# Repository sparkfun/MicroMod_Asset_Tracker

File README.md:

# MicroMod Asset Tracker Carrier Board

[*SparkFun MicroMod Asset Tracker Carrier Board (DEV-17272)*](https://www.sparkfun.com/products/17272)

The MicroMod Asset Tracker Carrier Board provides you with a toolkit to monitor and track the location of your assets. Built around the u-blox SARA-R510M8S module, the asset tracker offers Secure Cloud LTE-M data communication for multi-regional use and has an integrated u-blox M8 GNSS receiver for accurate positioning information. The SARA-R5 supports many different forms of data communication from full TCP/IP sockets and packet switched data, through HTTP Get/Put/Post, FTP (the SARA has a built-in file system), Ping, to good old SMS text messaging!

The Asset Tracker Carrier Board has an integrated ICM-20948 Inertial Measurement Unit (IMU) for Nine Degree-Of-Freedom orientation and movement detection. Want to send a message if your asset is moved? The Asset Tracker can do that! The board also has a built-in digital microphone and so can send an alert as soon as a noise is detected too.

The SparkFun Asset Tracker Carrier Board also has a built-in micro-SD card socket for data logging. Power options include both USB-C and LiPo battery (with built-in charging and battery fuel gauge), but you can provide power via a breakout pin too.

## Repository Contents

* **/Examples** - A set of examples demonstrating how to use each component on the Asset Tracker. Run these from the Arduino IDE.
* **/Documentation** - Datasheets etc.
* **/Hardware** - Eagle PCB, SCH and LBR design files. Full schematic in PDF format.
* **[LICENSE.md](./LICENSE.md)** - License details

## Documentation

* **[SparkFun u-blox SARA-R5 Arduino Library](https://github.com/sparkfun/SparkFun_u-blox_SARA-R5_Arduino_Library)** - An Arduino library for the SARA-R5 Module
* **[Hookup Guide](https://learn.sparkfun.com/tutorials/micromod-asset-tracker-carrier-board-hookup-guide)** - Basic Hookup Guide for the MicroMod Asset Tracker Carrier Board
* **[Getting Started with MicroMod](https://learn.sparkfun.com/tutorials/getting-started-with-micromod)** -  A tutorial to help you get started with the MicroMod Ecosystem.
* **[Designing with MicroMod](https://learn.sparkfun.com/tutorials/designing-with-micromod)** - A tutorial to walk you through the specs of the MicroMod processor and carrier board as well as the basics of incorporating the MicroMod form factor into your own PCB designs.

## Product Versions

* [DEV-17272](https://www.sparkfun.com/products/17272) - The MicroMod Asset Tracker Carrier Board uses the u-blox SARA-R5 LTE-M / NB-IoT module to provide a powerful development tool.

## License Information

This product is _**open source**_!

Please review the LICENSE.md file for license information.

If you have any questions or concerns on licensing, please contact technical support on our [SparkFun forums](https://forum.sparkfun.com/viewforum.php?f=152).

Distributed as-is; no warranty is given.

- Your friends at SparkFun.

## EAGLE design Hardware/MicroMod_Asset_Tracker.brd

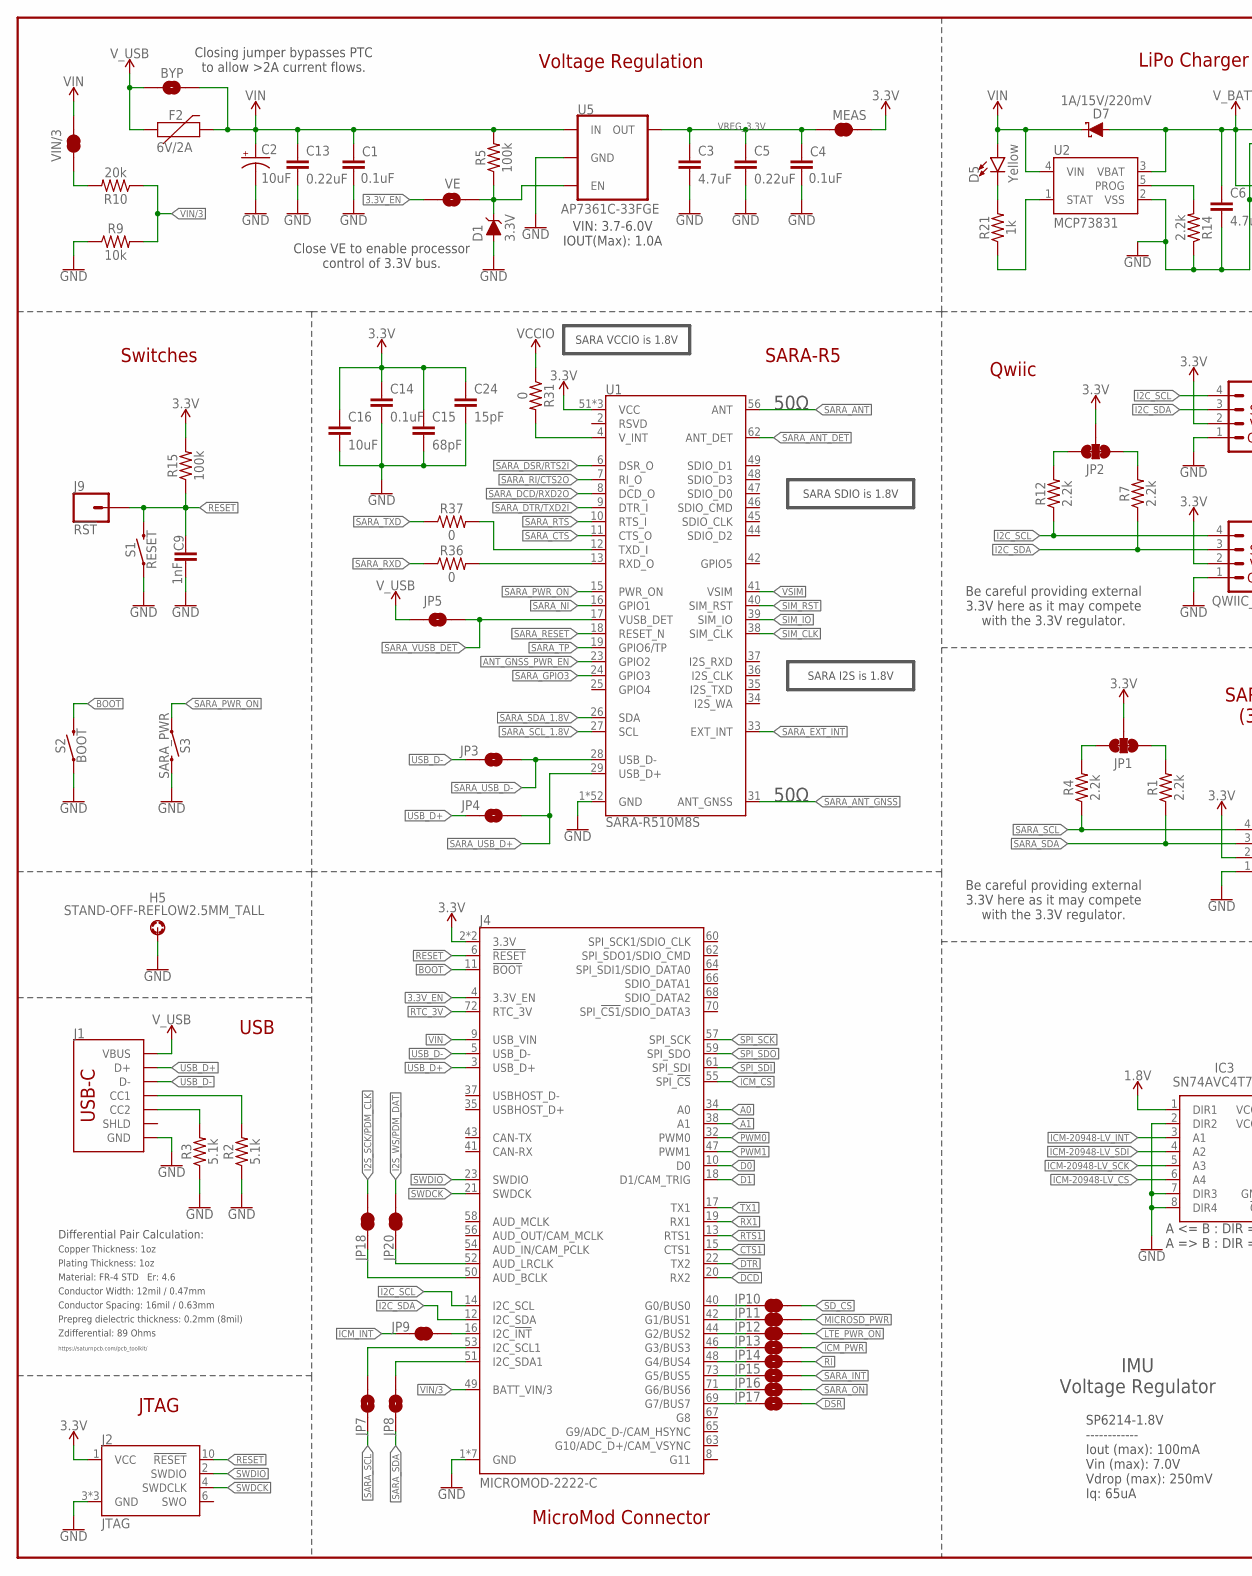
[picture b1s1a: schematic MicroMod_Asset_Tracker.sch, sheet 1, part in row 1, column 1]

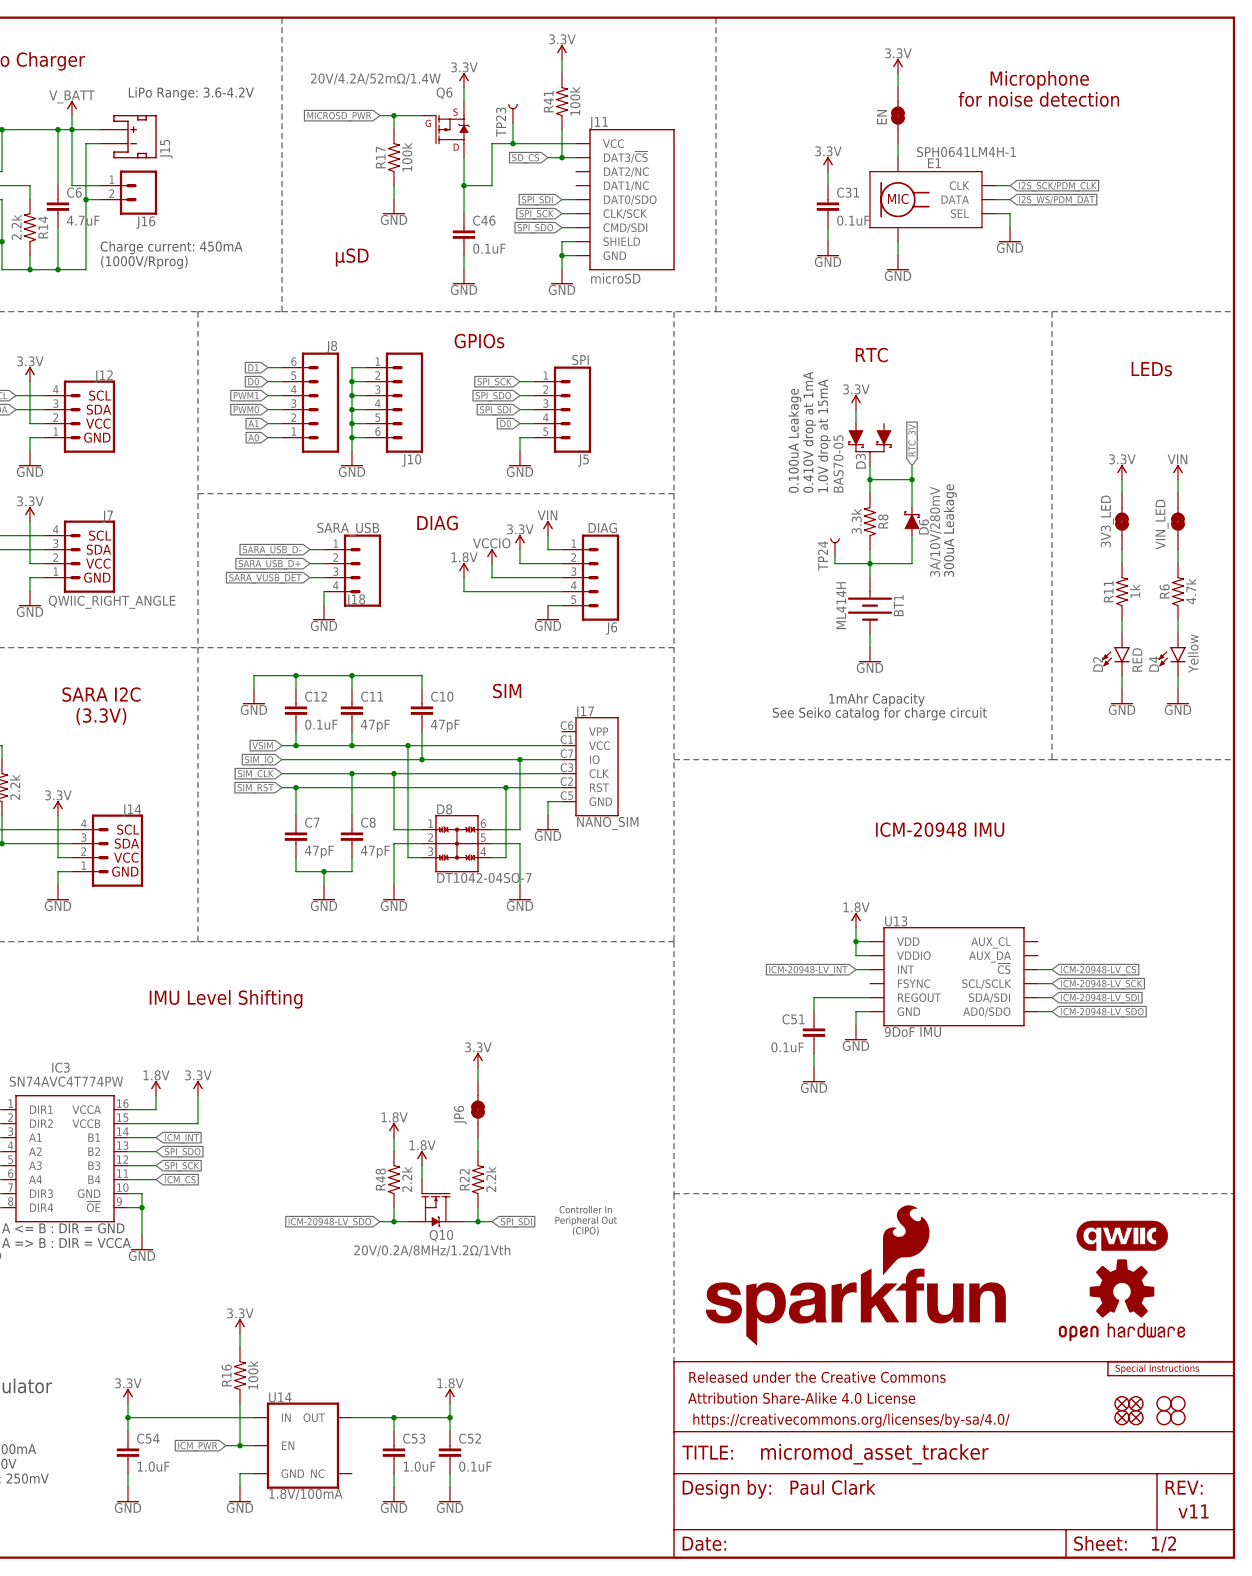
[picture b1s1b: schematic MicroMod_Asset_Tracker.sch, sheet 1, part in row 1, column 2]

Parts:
3V3_LED: JUMPER-SMT_2_NC_TRACE_SILK; SMT-JUMPER_2_NC_TRACE_SILK
BT1: ML414H; ML414H_IV01E
BYP: JUMPER-SMT_2_NO_SILK; SMT-JUMPER_2_NO_SILK
C1, C4, C12, C14, C31, C46, C51, C52: 0.1uF; 0603
C2: 10uF; EIA3216
C3, C6: 4.7uF; 0603
C5, C13: 0.22uF; 0603
C7, C8, C10, C11: 47pF; 0603
C9: 1nF; 0603
C15: 68pF; 0603
C16: 10uF; 0603
C24: 15pF; 0603
C53, C54: 1.0uF; 0603
D1: 3.3V; SOD-323
D2: RED; LED-0603
D3: BAS70-05; SOT23-3
D4, D5: Yellow; LED-0603
D6: 3A/10V/280mV; SOD-323
D7: 1A/15V/220mV; DO-214BA
D8: DT1042-04SO-7; SOT23-6L
E1: SPH0641LM4H-1; SPH0641LM4H-1_MICROPHONE
EN: JUMPER-SMT_2_NC_TRACE_SILK; SMT-JUMPER_2_NC_TRACE_SILK
F2: 6V/2A; 1210
FD1, FD2, FD3, FD4: FIDUCIALUFIDUCIAL; FIDUCIAL-MICRO
FRAME1: FRAME-LEDGER; CREATIVE_COMMONS
H1, H2, H3, H4: STAND-OFF
H5: STAND-OFF-REFLOW2.5MM_TALL; STAND-OFF-REFLOW-M2.5
IC3: SN74AVC4T774PW; SOP65P640X120-16N
J1: USB_C_4-LAYER_PADS; USB-C-16P_4LAYER-PADS
J2: JTAG; 2X5-PTH-1.27MM
J4: MICROMOD-2222-C; M.2-CONNECTOR-E
J5: SPI; 1X05_NO_SILK
J6: DIAG; 1X05_NO_SILK
J7: QWIIC_RIGHT_ANGLE; JST04_1MM_RA
J8, J10: CONN_06NO_SILK_NO_POP; 1X06_NO_SILK
J9: !RST!; 1X01_NO_SILK
J11: microSD; MICRO-SD-SOCKET
J12, J14: I2C_STANDARD_NO_SILK; 1X04_NO_SILK
J15: JST_2MM_MALE; JST-2-SMD
J16: CONN_021X02_NO_SILK; 1X02_NO_SILK
J17: NANO_SIM; NANO_SIM_WURTH_693043020611
J18: SARA_USB; 1X04_NO_SILK
JP1, JP2: JUMPER-SMT_3_2-NC_TRACE_SILK; SMT-JUMPER_3_2-NC_TRACE_SILK
JP3, JP4, JP5, JP7, JP8, JP13, JP14, JP15, JP16, JP17: JUMPER-SMT_2_NO_SILK; SMT-JUMPER_2_NO_SILK
JP6, JP9, JP10, JP11, JP12, JP18, JP20: JUMPER-SMT_2_NC_TRACE_SILK; SMT-JUMPER_2_NC_TRACE_SILK
LOGO1: SFE_LOGO_NAME_FLAME.1_INCH; SFE_LOGO_NAME_FLAME_.1
LOGO2: QWIIC_LOGO_CONNECTOR; QWIIC_5.5MM
LOGO3: OSHW-LOGOMINI; OSHW-LOGO-MINI
LOGO5: SPECIAL_INSTRUCTIONS-ORDERING; ORDERING_INSTRUCTIONS
MEAS: JUMPER-COMBO_2_NC_TRACE; COMBO-JUMPER_2_NC_TRACE
Q6: 20V/4.2A/52mΩ/1.4W; SOT23-3
Q10: 20V/0.2A/8MHz/1.2Ω/1Vth; SOT-416FL
R1, R4, R7, R12, R14, R22, R48: 2.2k; 0603
R2, R3: 5.1k; 0603
R5, R15, R16, R17, R41: 100k; 0603
R6: 4.7k; 0603
R8: 3.3k; 0603
R9: 10k; 0603
R10: 20k; 0603
R11, R21: 1k; 0603
R31, R36, R37: 0; 0603
S1: RESET; TACTILE_SWITCH_SMD_5.2MM
S2: BOOT; TACTILE_SWITCH_SMD_5.2MM
S3: SARA_PWR; TACTILE_SWITCH_SMD_5.2MM
TP23, TP24: TEST-POINT3; PAD.03X.03
U1: SARA-R510M8S; SARA-LGA
U2: MCP73831; SOT23-5
U5: AP7361C-33FGE; UDFN-8
U13: 9DoF IMU; QFN24-3X3-ICM-20948
U14: 1.8V/100mA; SC70
VE: JUMPER-SMT_2_NO_SILK; SMT-JUMPER_2_NO_SILK
VIN/3: JUMPER-SMT_2_NC_TRACE_SILK; SMT-JUMPER_2_NC_TRACE_SILK
VIN_LED: JUMPER-SMT_2_NC_TRACE_SILK; SMT-JUMPER_2_NC_TRACE_SILK

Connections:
1.8V: C52.1, C53.1, IC3.1 (DIR1), IC3.16 (VCCA), J6.4, Q10.1 (G), R48.2, U13.8 (VDDIO), U13.13 (VDD), U14.5 (OUT)
3.3V: 3V3_LED.2, C14.1, C15.1, C16.1, C24.1, C31.1, C54.1, D3.2 (A1), EN.2, IC3.15 (VCCB), J2.1 (VCC), J4.2 (3.3V), J4.74 (3.3V), J6.2, J7.2, J12.2, J14.2, JP1.2, JP2.2, JP6.2, MEAS.2, MEAS.4 (2), Q6.2 (S), R15.2, R16.2, R41.2, U1.51 (VCC), U1.52 (VCC), U1.53 (VCC), U14.1 (IN); also elsewhere on the board
3.3V_EN: J4.4 (3.3V_EN), VE.1
!BOOT!: J4.11 (!BOOT!), S2.3 (2), S2.4 (2)
!RESET!: C9.1, J2.10 (!RESET), J4.6 (!RESET!), J9.1, R15.1, S1.3 (2), S1.4 (2); also elsewhere on the board
A0: J4.34 (A0), J8.1
A1: J4.38 (A1), J8.2
ANT_GNSS_PWR_EN: U1.23 (GPIO2); also elsewhere on the board
CHG_LED: R21.1, U2.1 (STAT)
CTS1: J4.15 (CTS1); also elsewhere on the board
D0: J4.10 (D0), J5.4, J8.5
D1: J4.18 (D1/CAM_TRIG), J8.6
DCD: J4.20 (RX2); also elsewhere on the board
DSR: JP17.2; also elsewhere on the board
DTR: J4.22 (TX2); also elsewhere on the board
G0: J4.40 (G0/BUS0), JP10.1
G1: J4.42 (G1/BUS1), JP11.1
G2: J4.44 (G2/BUS2), JP12.1
G3: J4.46 (G3/BUS3), JP13.1
G4: J4.48 (G4/BUS4), JP14.1
G5: J4.73 (G5/BUS5), JP15.1
G6: J4.71 (G6/BUS6), JP16.1
G7: J4.69 (G7/BUS7), JP17.1
GND: BT1.-, C1.2, C2.-, C3.2, C4.2, C5.2, C6.2, C7.2, C8.2, C9.2, C10.1, C11.1, C12.1, C13.2, C14.2, C15.2, C16.2, C24.2, C31.2, C46.2, C51.2, C52.2, C53.2, C54.2, D1.A, D2.C, D4.C, D8.2, D8.5, E1.2 (SEL), E1.3 (GND), E1.6 (GND), E1.7 (GND), E1.8 (GND), H5.1, IC3.2 (DIR2), IC3.7 (DIR3), IC3.8 (DIR4), IC3.9 (!OE), IC3.10 (GND), J1.GND, J1.GND2 (GND), J2.3 (GND), J2.5 (GND), J2.9 (GND), J4.1 (GND), J4.7 (GND), J4.33 (GND), J4.36 (GND), J4.39 (GND), J4.45 (GND), J4.75 (GND), J5.5, J6.5, J7.1, J10.1, J10.2, J10.3, J10.4, J10.5, J10.6, J11.CD1 (SHIELD), J11.GND, J11.GND1 (GND), J11.GND3 (GND), J12.1, J14.1, J15.1 (-), J16.2, J17.C5 (GND), J18.4, R2.1, R3.1, R9.1, R14.1, R17.1, S1.1, S1.2 (1), S2.1, S2.2 (1), S3.3 (2), S3.4 (2), U1.1 (GND), U1.3 (GND), U1.5 (GND), U1.14 (GND), U1.20 (GND), U1.21 (GND), U1.22 (GND), U1.30 (GND), U1.32 (GND), U1.43 (GND), U1.50 (GND), U1.54 (GND), U1.55 (GND), U1.57 (GND), U1.58 (GND), U1.59 (GND), U1.60 (GND), U1.61 (GND), U1.63 (GND), U1.64 (GND), U1.65 (GND), U1.66 (GND), U1.67 (GND), U1.68 (GND), U1.69 (GND), U1.70 (GND), U1.71 (GND), U1.72 (GND), U1.73 (GND), U1.74 (GND), U1.75 (GND), U1.76 (GND), U1.77 (GND), U1.78 (GND), U1.79 (GND), U1.80 (GND), U1.81 (GND), U1.82 (GND), U1.83 (GND), U1.84 (GND), U1.85 (GND), U1.86 (GND), U1.87 (GND), U1.88 (GND), U1.89 (GND), U1.90 (GND), U1.91 (GND), U1.92 (GND), U1.93 (GND), U1.94 (GND), U1.95 (GND), U1.96 (GND), U2.2 (VSS), U5.4 (GND), U5.EP (GND), U13.18 (GND), U13.20 (GND), U14.2 (GND); also elsewhere on the board
I2C_SCL: J4.14 (I2C_SCL), J7.4, J12.4, R12.1; also elsewhere on the board
I2C_SDA: J4.12 (I2C_SDA), J7.3, J12.3, R7.1; also elsewhere on the board
I2S_SCK/PDM_CLK: E1.4 (CLK), JP18.2
I2S_WS/PDM_DAT: E1.1 (DATA), JP20.2
ICM-20948-LV_!CS!: IC3.6 (A4), U13.22 (!CS)
ICM-20948-LV_INT: IC3.3 (A1), U13.12 (INT)
ICM-20948-LV_SCK: IC3.5 (A3), U13.23 (SCL/SCLK)
ICM-20948-LV_SDI: IC3.4 (A2), U13.24 (SDA/SDI)
ICM-20948-LV_SDO: Q10.2 (S), R48.1, U13.9 (AD0/SDO)
ICM_!CS!: IC3.11 (B4), J4.55 (SPI_!CS!)
ICM_INT: IC3.14 (B1), JP9.1
ICM_PWR: JP13.2, R16.1, U14.3 (EN)
LTE_PWR_ON: JP12.2; also elsewhere on the board
MICROSD_PWR: JP11.2, Q6.1 (G), R17.2
unnamed: R6.2, VIN_LED.1
unnamed: JP1.3, R4.2
unnamed: JP1.1, R1.2
unnamed: E1.5 (VDD), EN.1
unnamed: J4.53 (I2C_SCL1), JP7.2
unnamed: 3V3_LED.1, R11.2
unnamed: D2.A, R11.1
unnamed: D4.A, R6.1
unnamed: JP2.3, R12.2
unnamed: J1.A5 (CC1), R2.2
unnamed: J1.B5 (CC2), R3.2
unnamed: D1.C, R5.1, U5.5 (EN), VE.2
unnamed: JP2.1, R7.2
unnamed: BT1.+, D6.A, R8.1, TP24.P$1
unnamed: J4.51 (I2C_SDA1), JP8.2
unnamed: R10.2, VIN/3.1
unnamed: J4.16 (I2C_!INT!), JP9.2
unnamed: R14.2, U2.5 (PROG)
unnamed: D5.C, R21.2
unnamed: JP6.1, R22.2
unnamed: C51.1, U13.10 (REGOUT)
unnamed: R31.2, U1.4 (V_INT)
unnamed: R36.2, U1.13 (RXD_O)
unnamed: R37.2, U1.12 (TXD_I)
unnamed: J4.52 (AUD_LRCLK), JP20.1
unnamed: J4.50 (AUD_BCLK), JP18.1
PWM0: J4.32 (PWM0), J8.3
PWM1: J4.47 (PWM1), J8.4
RI: JP14.2; also elsewhere on the board
RTC_3V: D3.3 (C), D6.C, J4.72 (RTC_3V), R8.2
RTS1: J4.13 (RTS1); also elsewhere on the board
RX1: J4.19 (RX1); also elsewhere on the board
SARA_!ON!: JP16.2; also elsewhere on the board
SARA_!RESET!: U1.18 (RESET_N); also elsewhere on the board
SARA_ANT: U1.56 (ANT); also elsewhere on the board
SARA_ANT_DET: U1.62 (ANT_DET); also elsewhere on the board
SARA_ANT_GNSS: U1.31 (ANT_GNSS); also elsewhere on the board
SARA_CTS: U1.11 (CTS_O); also elsewhere on the board
SARA_DCD/RXD2O: U1.8 (DCD_O); also elsewhere on the board
SARA_DSR/RTS2I: U1.6 (DSR_O); also elsewhere on the board
SARA_DTR/TXD2I: U1.9 (DTR_I); also elsewhere on the board
SARA_EXT_INT: U1.33 (EXT_INT); also elsewhere on the board
SARA_GPIO3: U1.24 (GPIO3); also elsewhere on the board
SARA_INT: JP15.2; also elsewhere on the board
SARA_NI: U1.16 (GPIO1); also elsewhere on the board
SARA_PWR_ON: S3.1, S3.2 (1), U1.15 (PWR_ON); also elsewhere on the board
SARA_RI/CTS2O: U1.7 (RI_O); also elsewhere on the board
SARA_RTS: U1.10 (RTS_I); also elsewhere on the board
SARA_RXD: R36.1; also elsewhere on the board
SARA_SCL: J14.4, JP7.1, R4.1; also elsewhere on the board
SARA_SCL_1.8V: U1.27 (SCL); also elsewhere on the board
SARA_SDA: J14.3, JP8.1, R1.1; also elsewhere on the board
SARA_SDA_1.8V: U1.26 (SDA); also elsewhere on the board
SARA_TP: U1.19 (GPIO6/TP); also elsewhere on the board
SARA_TXD: R37.1; also elsewhere on the board
SARA_USB_D+: J18.2, JP4.2, U1.29 (USB_D+)
SARA_USB_D-: J18.1, JP3.2, U1.28 (USB_D-)
SARA_VUSB_DET: J18.3, JP5.2, U1.17 (VUSB_DET)
SD_!CS!: J11.CS/DAT3 (DAT3/!CS!), JP10.2, R41.1
SD_PWR: C46.1, J11.VCC, Q6.3 (D), TP23.P$1
SIM_CLK: C8.1, D8.1, J17.C3 (CLK), U1.38 (SIM_CLK)
SIM_IO: C10.2, D8.6, J17.C7 (IO), U1.39 (SIM_IO)
SIM_RST: C7.1, D8.4, J17.C2 (RST), U1.40 (SIM_RST)
SPI_SCK: IC3.12 (B3), J4.57 (SPI_SCK), J5.1, J11.SCLK (CLK/SCK)
SPI_SDI: J4.61 (SPI_SDI), J5.3, J11.DO/DAT0 (DAT0/SDO), Q10.3 (D), R22.1
SPI_SDO: IC3.13 (B2), J4.59 (SPI_SDO), J5.2, J11.DI/CMD (CMD/SDI)
SWDCK: J2.4 (SWDCLK), J4.21 (SWDCK)
SWDIO: J2.2 (SWDIO), J4.23 (SWDIO)
TX1: J4.17 (TX1); also elsewhere on the board
USB_D+: J1.A6 (D+), J1.B6 (D+), J4.3 (USB_D+), JP4.1
USB_D-: J1.A7 (D-), J1.B7 (D-), J4.5 (USB_D-), JP3.1
VCCIO: J6.3, R31.1; also elsewhere on the board
VIN: BYP.2, C1.1, C2.+, C13.1, D5.A, D7.C, F2.2, J4.9 (USB_VIN), J6.1, R5.2, U2.4 (VIN), U5.8 (IN), VIN/3.2, VIN_LED.2; also elsewhere on the board
VIN/3: J4.49 (BATT_VIN/3), R9.2, R10.1
VREG_3.3V: C3.1, C4.1, C5.1, MEAS.1, MEAS.3 (1), U5.1 (OUT)
VSIM: C11.2, C12.2, D8.3, J17.C1 (VCC), U1.41 (VSIM)
V_BATT: C6.1, D7.A, J15.2 (+), J16.1, U2.3 (VBAT); also elsewhere on the board
V_USB: BYP.1, F2.1, J1.VBUS1 (VBUS), J1.VBUS2 (VBUS), JP5.1

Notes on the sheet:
μSD
300uA Leakage
See Seiko catalog for charge circuit
1mAhr Capacity
Closing jumper bypasses PTC to allow >2A current flows.
JTAG
USB
GPIOs
Microphone for noise detection
RTC
Voltage Regulation
MicroMod Connector
0.100uA Leakage 0.410V drop at 1mA 1.0V drop at 15mA
Paul Clark
v11
VIN: 3.7-6.0V IOUT(Max): 1.0A
Be careful providing external 3.3V here as it may compete with the 3.3V regulator.
Close VE to enable processor control of 3.3V bus.
Qwiic
LEDs
Switches
SARA-R5
ICM-20948 IMU
IMU Voltage Regulator
IMU Level Shifting
SP6214-1.8V ------------ Iout (max): 100mA Vin (max): 7.0V Vdrop (max): 250mV Iq: 65uA
Controller In Peripheral Out (CIPO)
LiPo Charger
LiPo Range: 3.6-4.2V
Charge current: 450mA (1000V/Rprog)
SIM
SARA SDIO is 1.8V
50Ω
SARA I2S is 1.8V
DIAG
SARA I2C (3.3V)
SARA VCCIO is 1.8V
Plating Thickness: 1oz
Material: FR-4 STD Er: 4.6
Copper Thickness: 1oz

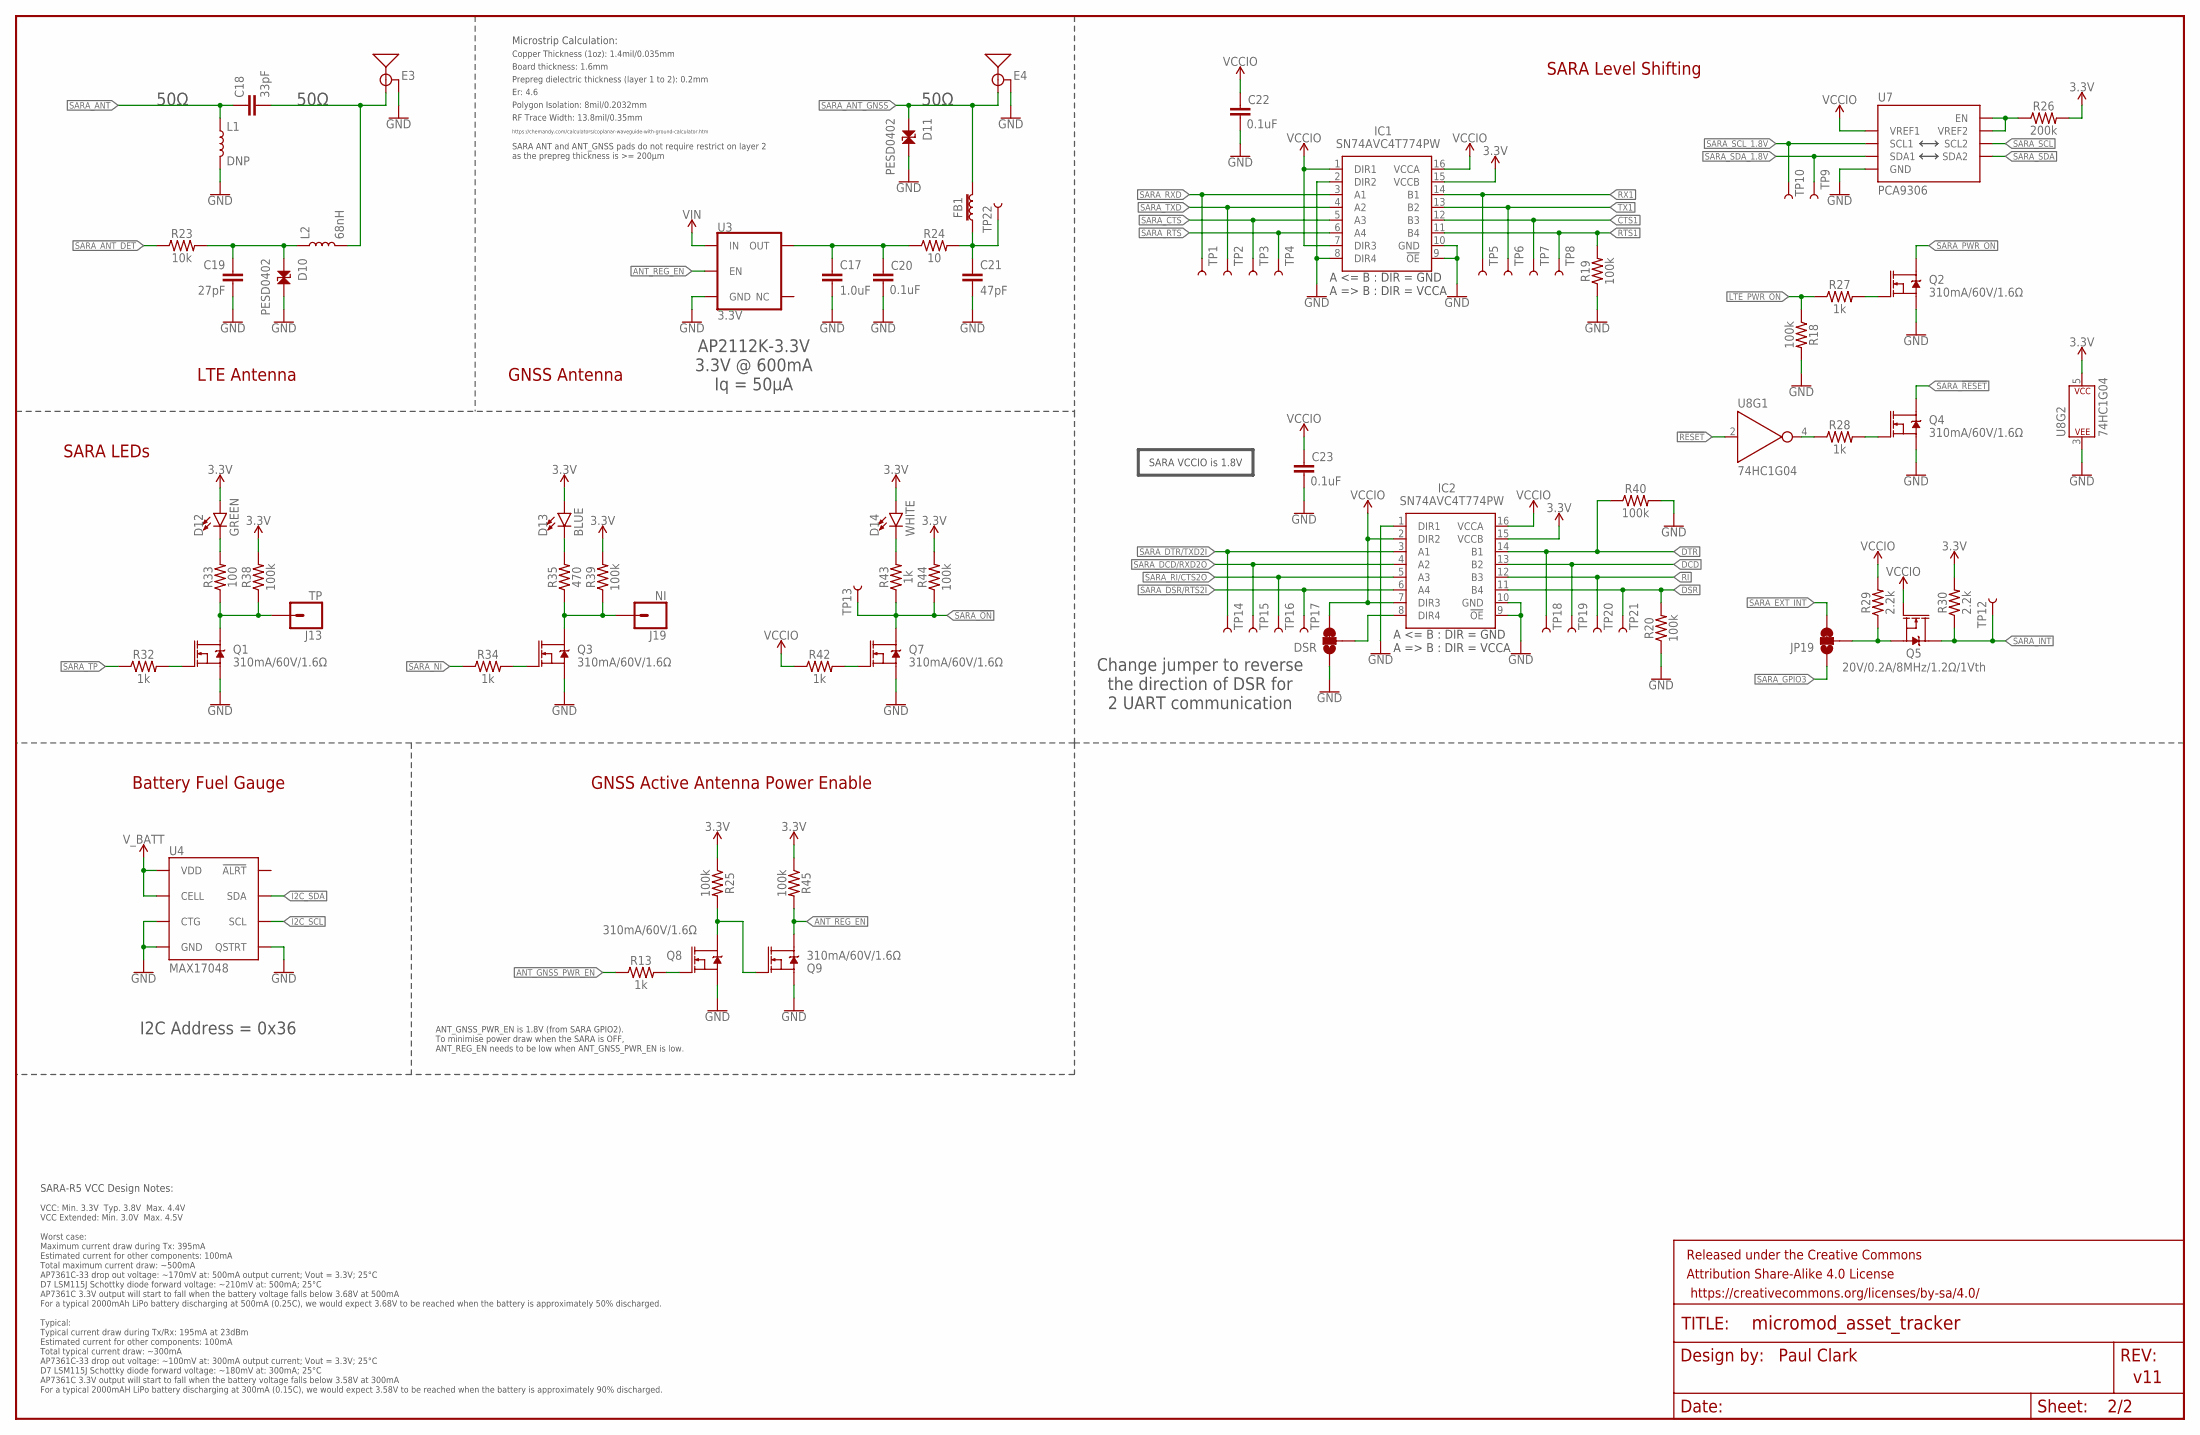
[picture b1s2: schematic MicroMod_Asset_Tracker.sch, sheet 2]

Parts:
C17: 1.0uF; 0603
C18: 33pF; 0402
C19: 27pF; 0402
C20, C22, C23: 0.1uF; 0603
C21: 47pF; 0603
D10, D11: PESD0402; 0402
D12: GREEN; LED-0603
D13: BLUE; LED-0603
D14: WHITE; LED-0603
DSR: JUMPER-SMT_3_1-NC_TRACE_SILK; SMT-JUMPER_3_1-NC_TRACE_SILK
E3, E4: ANTENNA-SMA-GROUNDEDEDGE_SMA_SMD; SMA-EDGE-SMD
FB1: 30Ω/1.8A; 0603
FRAME2: FRAME-LEDGER; CREATIVE_COMMONS
IC1, IC2: SN74AVC4T774PW; SOP65P640X120-16N
J13: TP; 1X01_NO_SILK
J19: NI; 1X01_NO_SILK
JP19: JUMPER-SMT_3_1-NC_TRACE_SILK; SMT-JUMPER_3_1-NC_TRACE_SILK
L1: DNP; 0402_COILCRAFT
L2: 68nH; 0402_COILCRAFT
Q1, Q2, Q3, Q4, Q7, Q8, Q9: 310mA/60V/1.6Ω; SOT323
Q5: 20V/0.2A/8MHz/1.2Ω/1Vth; SOT-416FL
R13, R27, R28, R32, R34, R42, R43: 1k; 0603
R18, R19, R20, R25, R38, R39, R40, R44, R45: 100k; 0603
R23: 10k; 0603
R24: 10; 0603
R26: 200k; 0603
R29, R30: 2.2k; 0603
R33: 100; 0603
R35: 470; 0603
TP1, TP2, TP3, TP4, TP5, TP6, TP7, TP8, TP9, TP10, TP12, TP13, TP14, TP15, TP16, TP17, TP18, TP19, TP20, TP21, TP22: TEST-POINT3; PAD.03X.03
U3: 3.3V; SOT23-5
U4: MAX17048; DFN-8
U7: PCA9306; VSSOP_8PIN
U8: 74HC1G04; SOT353

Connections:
3.3V: D12.A, D13.A, D14.A, IC1.15 (VCCB), IC2.15 (VCCB), R25.1, R26.2, R30.2, R38.2, R39.2, R44.2, R45.1, U8.5 (P$V+); also elsewhere on the board
!RESET!: U8.2 (A); also elsewhere on the board
ANT_GNSS_PWR_EN: R13.1; also elsewhere on the board
ANT_REG_EN: Q9.3 (D), R45.2, U3.3 (EN)
CTS1: IC1.12 (B3), TP7.P$1; also elsewhere on the board
DCD: IC2.13 (B2), TP19.P$1; also elsewhere on the board
DSR: IC2.11 (B4), R20.2, TP21.P$1; also elsewhere on the board
DTR: IC2.14 (B1), R40.1, TP18.P$1; also elsewhere on the board
GND: C17.2, C19.2, C20.2, C21.2, C22.2, C23.2, D10.2, D11.2, DSR.1, E3.GND@0 (GND), E3.GND@1 (GND), E4.GND@0 (GND), E4.GND@1 (GND), IC1.2 (DIR2), IC1.8 (DIR4), IC1.9 (!OE), IC1.10 (GND), IC2.1 (DIR1), IC2.9 (!OE), IC2.10 (GND), L1.P$2 (2), Q1.2 (S), Q2.2 (S), Q3.2 (S), Q4.2 (S), Q7.2 (S), Q8.2 (S), Q9.2 (S), R18.2, R19.1, R20.1, R40.2, U3.2 (GND), U4.1 (CTG), U4.4 (GND), U4.6 (QSTRT), U4.9 (GND), U7.P1 (GND), U8.3 (P$V-); also elsewhere on the board
I2C_SCL: U4.7 (SCL); also elsewhere on the board
I2C_SDA: U4.8 (SDA); also elsewhere on the board
LTE_PWR_ON: R18.1, R27.1; also elsewhere on the board
unnamed: C18.2, E3.SIG (SIGNAL), L2.P$2 (2)
unnamed: C19.1, D10.1, L2.P$1 (1), R23.2
unnamed: R26.1, U7.P7 (VREF2), U7.P8 (EN)
unnamed: DSR.2, IC2.8 (DIR4)
unnamed: C17.1, C20.1, R24.1, U3.5 (OUT)
unnamed: C21.1, FB1.1, R24.2, TP22.P$1
unnamed: Q2.1 (G), R27.2
unnamed: Q4.1 (G), R28.2
unnamed: R28.1, U8.4 (Y)
unnamed: Q1.1 (G), R32.2
unnamed: J13.1, Q1.3 (D), R33.1, R38.1
unnamed: D12.C, R33.2
unnamed: Q3.1 (G), R34.2
unnamed: J19.1, Q3.3 (D), R35.1, R39.1
unnamed: D13.C, R35.2
unnamed: Q8.1 (G), R13.2
unnamed: Q8.3 (D), Q9.1 (G), R25.2
unnamed: JP19.2, Q5.2 (S), R29.1
unnamed: Q7.1 (G), R42.2
unnamed: D14.C, R43.2
RI: IC2.12 (B3), TP20.P$1; also elsewhere on the board
RTS1: IC1.11 (B4), R19.2, TP8.P$1; also elsewhere on the board
RX1: IC1.14 (B1), TP5.P$1; also elsewhere on the board
SARA_!ON!: Q7.3 (D), R43.1, R44.1, TP13.P$1; also elsewhere on the board
SARA_!RESET!: Q4.3 (D); also elsewhere on the board
SARA_ANT: C18.1, L1.P$1 (1); also elsewhere on the board
SARA_ANT_DET: R23.1; also elsewhere on the board
SARA_ANT_GNSS: D11.1, E4.SIG (SIGNAL), FB1.2; also elsewhere on the board
SARA_CTS: IC1.5 (A3), TP3.P$1; also elsewhere on the board
SARA_DCD/RXD2O: IC2.4 (A2), TP15.P$1; also elsewhere on the board
SARA_DSR/RTS2I: IC2.6 (A4), TP17.P$1; also elsewhere on the board
SARA_DTR/TXD2I: IC2.3 (A1), TP14.P$1; also elsewhere on the board
SARA_EXT_INT: JP19.3; also elsewhere on the board
SARA_GPIO3: JP19.1; also elsewhere on the board
SARA_INT: Q5.3 (D), R30.1, TP12.P$1; also elsewhere on the board
SARA_NI: R34.1; also elsewhere on the board
SARA_PWR_ON: Q2.3 (D); also elsewhere on the board
SARA_RI/CTS2O: IC2.5 (A3), TP16.P$1; also elsewhere on the board
SARA_RTS: IC1.6 (A4), TP4.P$1; also elsewhere on the board
SARA_RXD: IC1.3 (A1), TP1.P$1; also elsewhere on the board
SARA_SCL: U7.P6 (SCL2); also elsewhere on the board
SARA_SCL_1.8V: TP10.P$1, U7.P3 (SCL1); also elsewhere on the board
SARA_SDA: U7.P5 (SDA2); also elsewhere on the board
SARA_SDA_1.8V: TP9.P$1, U7.P4 (SDA1); also elsewhere on the board
SARA_TP: R32.1; also elsewhere on the board
SARA_TXD: IC1.4 (A2), TP2.P$1; also elsewhere on the board
TX1: IC1.13 (B2), TP6.P$1; also elsewhere on the board
VCCIO: C22.1, C23.1, DSR.3, IC1.1 (DIR1), IC1.7 (DIR3), IC1.16 (VCCA), IC2.2 (DIR2), IC2.7 (DIR3), IC2.16 (VCCA), Q5.1 (G), R29.2, R42.1, U7.P2 (VREF1); also elsewhere on the board
VIN: U3.1 (IN); also elsewhere on the board
V_BATT: U4.2 (CELL), U4.3 (VDD); also elsewhere on the board

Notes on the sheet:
Paul Clark
v11
Board thickness: 1.6mm
Er: 4.6
Copper Thickness (1oz): 1.4mil/0.035mm
RF Trace Width: 13.8mil/0.35mm
Polygon Isolation: 8mil/0.2032mm
Prepreg dielectric thickness (layer 1 to 2): 0.2mm
https://chemandy.com/calculators/coplanar-waveguide-with-ground-calculator.htm
Microstrip Calculation:
50Ω
LTE Antenna
GNSS Antenna
SARA Level Shifting
SARA LEDs
SARA ANT and ANT_GNSS pads do not require restrict on layer 2 as the prepreg thickness is >= 200µm
SARA-R5 VCC Design Notes:
VCC: Min. 3.3V Typ. 3.8V Max. 4.4V VCC Extended: Min. 3.0V Max. 4.5V Worst case: Maximum current draw during Tx: 395mA Estimated current for other components: 100mA Total maximum current draw: ~500mA AP7361C-33 drop out voltage: ~170mV at: 500mA output current; Vout = 3.3V; 25°C D7 LSM115J Schottky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
AP2112K-3.3V 3.3V @ 600mA Iq = 50µA
Battery Fuel Gauge
I2C Address = 0x36
Change jumper to reverse the direction of DSR for 2 UART communication
GNSS Active Antenna Power Enable
ANT_GNSS_PWR_EN is 1.8V (from SARA GPIO2). To minimise power draw when the SARA is OFF, ANT_REG_EN needs to be low when ANT_GNSS_PWR_EN is low.
SARA VCCIO is 1.8V

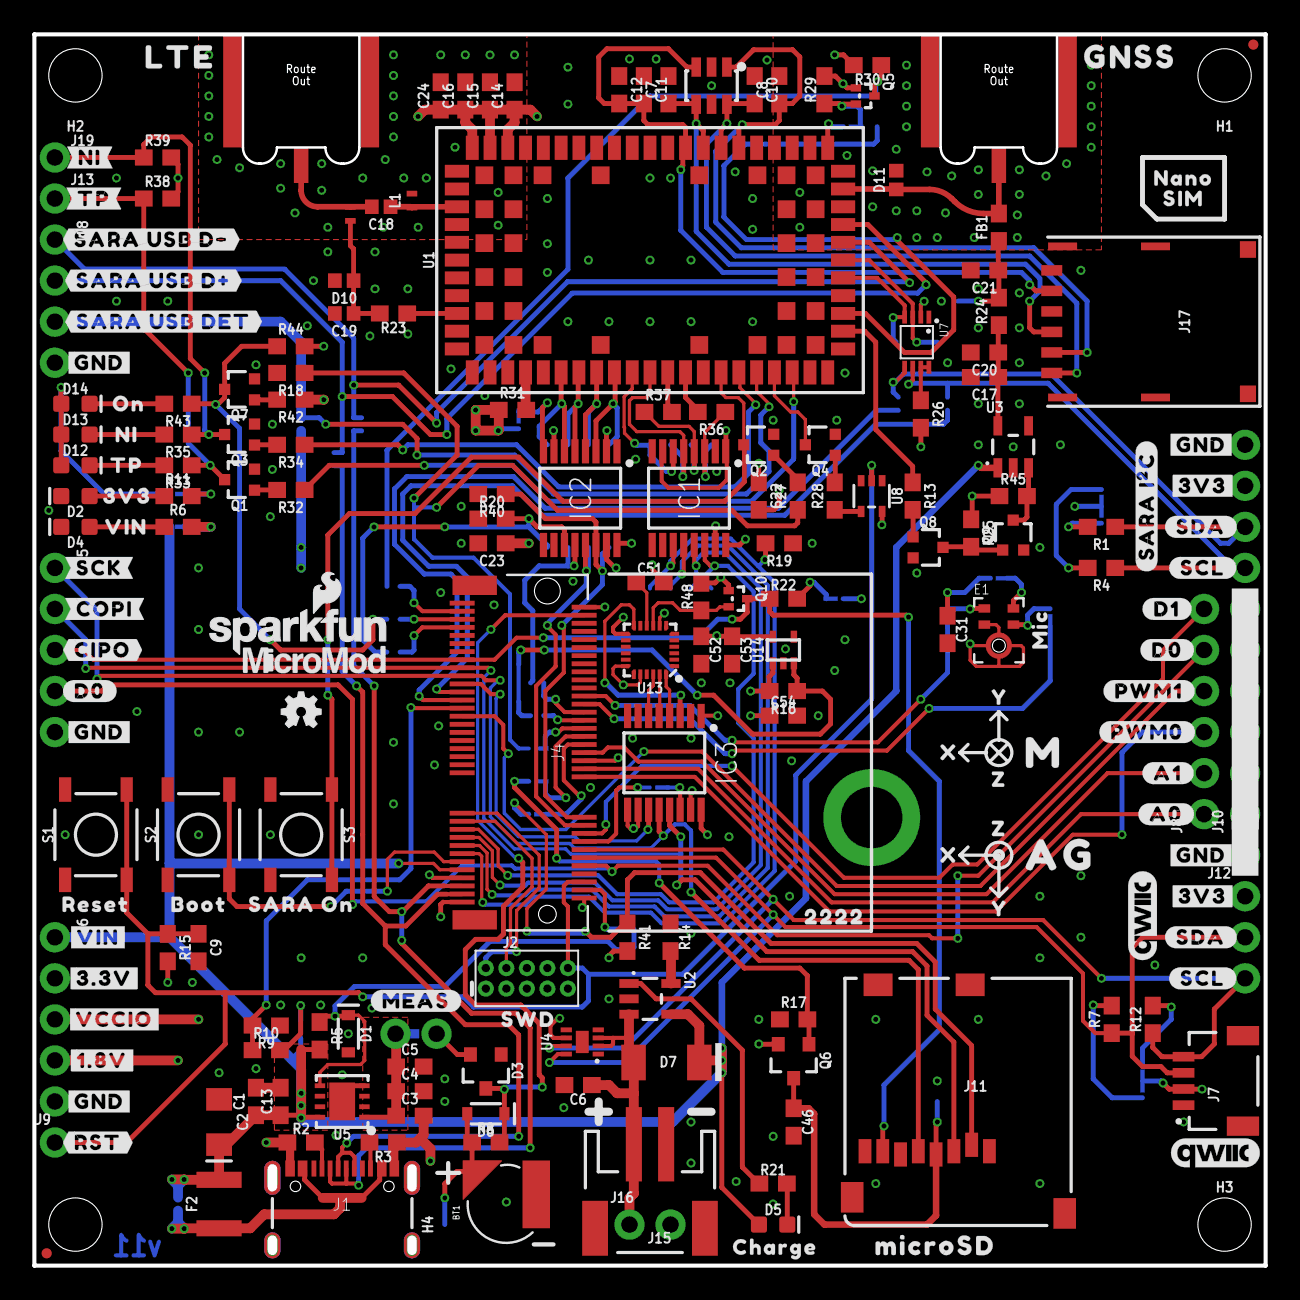
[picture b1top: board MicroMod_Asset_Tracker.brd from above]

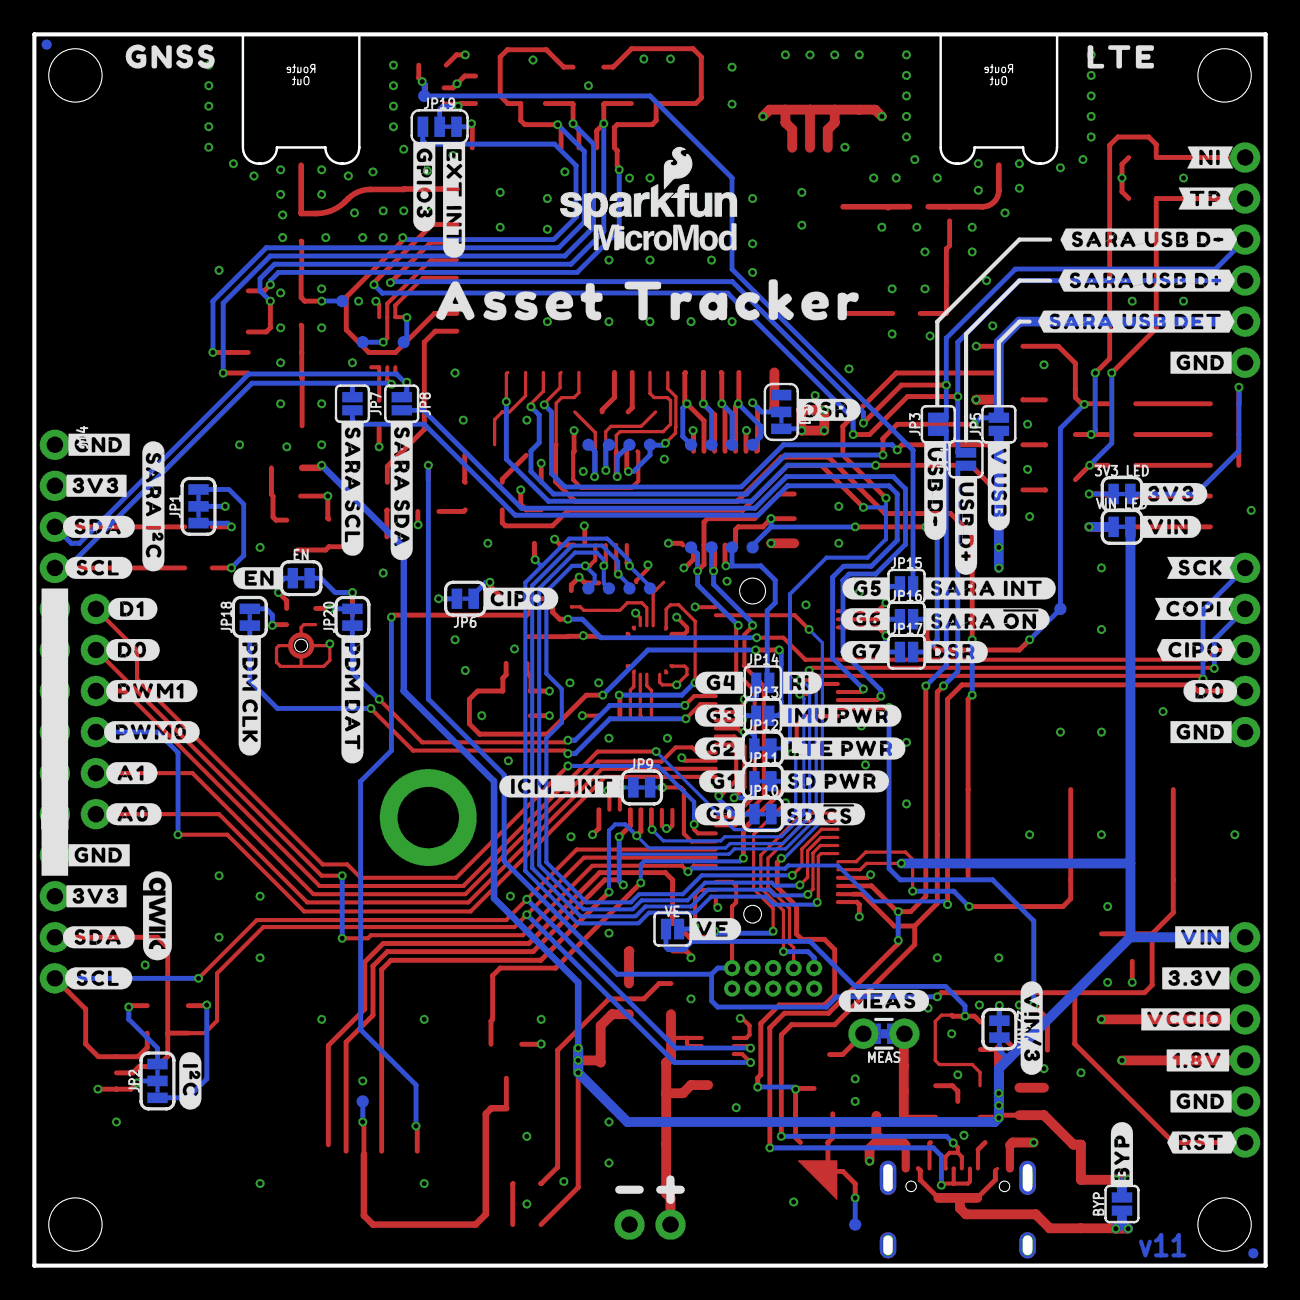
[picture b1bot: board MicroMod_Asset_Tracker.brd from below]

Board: 4 copper layers, 76.2 x 76.2 mm, 340 parts (128 on the bottom side), 137 nets.

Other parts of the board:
LOGO4: SFE_LOGO_NAME_FLAME.1_INCH; SFE_LOGO_NAME_FLAME_.1
LOGO6, LOGO7: QWIIC_LOGO_CONNECTOR; QWIIC_5.5MM
U$1: #EN#0
U$2: MIC0
U$3, U$11, U$13, U$14: #3V3#1
U$4: #3V3#0
U$5, U$23: #SARA_I�C#0
U$6, U$7: #A0#5
U$8, U$9: #A1#4
U$10, U$25, U$35, U$68: #D0#1
U$12, U$15, U$16, U$22: #GND#0
U$17, U$86: #RST#1
U$18: #VE#0
U$19, U$87: #MEAS#2
U$20: #VIN#1
U$21: SWD0
U$24, U$34: MICROMOD_LOGO_.35
U$26, U$27, U$43, U$44: #SCL#3
U$28: MICROSD0
U$29, U$31: #D1#0
U$30, U$37, U$50, U$51: #SDA#2
U$32, U$41: #PWM0#3
U$33: #BYP#1
U$36: 3V37
U$38, U$48: Y2
U$39, U$47: X1
U$40: BOOT5
U$42, U$49: #PWM1#2
U$45: RESET6
U$46: VIN8
U$52, U$54: Z0
U$53: #I�C#0
U$55, U$56, U$73, U$74, U$81, U$82: #GND#4
U$57, U$58: #TP#0
U$59, U$60: #NI#0
U$61, U$62, U$63, U$64: #SARA_USB_D##0
U$65, U$66: #SARA_USB_DET#0
U$67, U$75: #VIN#0
U$69, U$70: #CIPO#2
U$71, U$72: #COPI#1
U$76, U$79: #3#3V#0
U$77, U$78: #SCK#0
U$80, U$83: #VCCIO#0
U$84, U$85: #1#8V#0
U$88, U$89: LTE0
U$90: NI0
U$91: TP0
U$92, U$93: #USB_D##0
U$94: #V_USB#0
U$95: AG0
U$96: M0
U$97: CHARGE0
U$98: ASSET_TRACKER0
U$99, U$100: GNSS0
U$101: ON0
U$102, U$105: #DSR#0
U$103: #SARA_INT#0
U$104: #RI#0
U$106: #SD_#CS##0
U$107: #IMU_PWR#0
U$108: #LTE_PWR#0
U$109: #SD_PWR#0
U$110: #SARA_#ON##0
U$111: #SARA_SCL#0
U$112: #SARA_SDA#0
U$113: SARA_ON0
U$114: #CIPO#0
U$115: 22220
U$116: #PDM_CLK#0
U$117: #PDM_DAT#0
U$118: #EXT_INT#0
U$119: #GPIO3#0
U$122: #G0#0
U$123: #G1#0
U$124: #G2#0
U$125: #G3#0
U$126: #G4#0
U$127: #G7#0
U$128: #G6#0
U$129: #G5#0
U$130: NANO0
U$131: SIM0
U$133: #VIN#3#0
U$134: #ICM_INT#0

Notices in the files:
parts and their libraries:
SparkFun-Aesthetics: Licensing: Creative Commons ShareAlike 4.0 International - https://creativecommons.org/licenses/by-sa/4.0
SparkFun-Aesthetics: Released under the Creative Commons Attribution Share-Alike 4.0 License
SparkFun-Aesthetics: https://creativecommons.org/licenses/by-sa/4.0
